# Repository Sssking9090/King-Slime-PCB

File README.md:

# King-Slime-PCB

 The project is a model of the King slime in Terraria. It also has the added function of vibrating and lighting up when the switch is clicked.
 
## Bill of meterials 
-  Resistors 6x
- 5mm LED 6x
 - mini motor disc
 - 6mm push button
 - CR2032 battery cell

Slack username: Sam

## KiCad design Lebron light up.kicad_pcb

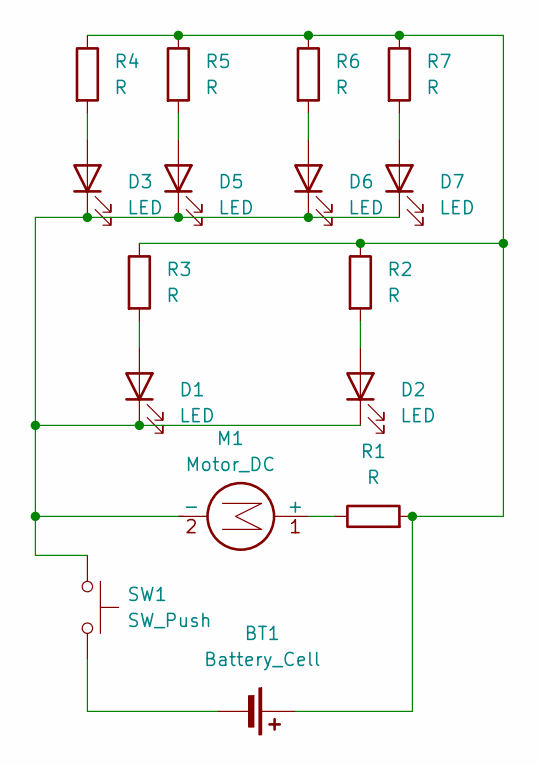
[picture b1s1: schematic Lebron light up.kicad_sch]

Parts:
BT1: Battery_Cell; BatteryHolder_Keystone_3034_1x20mm
D1, D2, D3, D5, D6, D7: LED; LED_D5.0mm
M1: Motor_DC; PinHeader_1x02_P2.54mm_Vertical
R1, R2, R3, R4, R5, R6, R7: R; R_Axial_DIN0207_L6.3mm_D2.5mm_P7.62mm_Horizontal
SW1: SW_Push; SW_PUSH_6mm

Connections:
unnamed: BT1.1 (+), R1.2, R2.1, R3.1, R4.1, R5.1, R6.1, R7.1
unnamed: BT1.2 (-), SW1.1
unnamed: D1.2 (A), R3.2
unnamed: D1.1 (K), D2.1 (K), D3.1 (K), D5.1 (K), D6.1 (K), D7.1 (K), M1.2 (-), SW1.2
unnamed: D2.2 (A), R2.2
unnamed: D3.2 (A), R4.2
unnamed: D5.2 (A), R5.2
unnamed: D6.2 (A), R6.2
unnamed: D7.2 (A), R7.2
unnamed: M1.1 (+), R1.1

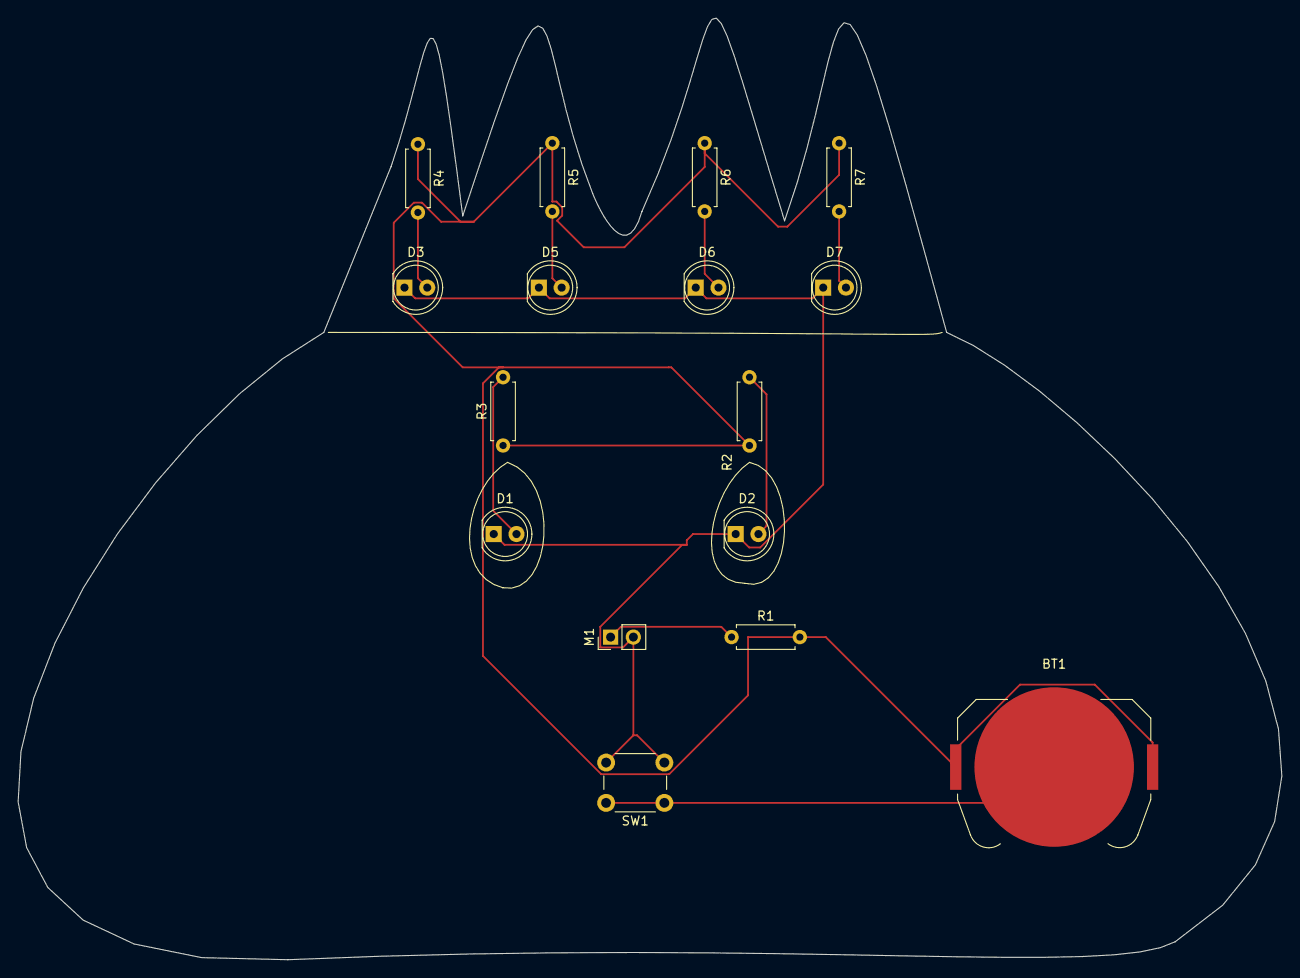
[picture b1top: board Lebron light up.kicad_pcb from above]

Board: 2 copper layers, 141.0 x 105.1 mm, 16 parts (0 on the bottom side), 10 nets.

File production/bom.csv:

Designator,Footprint,Quantity,Value,LCSC Part #
BT1,BatteryHolder_Keystone_3034_1x20mm,1,Battery_Cell,
"D1, D2, D3, D5, D6, D7",LED_D5.0mm,6,LED,
M1,PinHeader_1x02_P2.54mm_Vertical,1,Motor_DC,
"R1, R2, R3, R4, R5, R6, R7",R_Axial_DIN0207_L6.3mm_D2.5mm_P7.62mm_Horizontal,7,R,
SW1,SW_PUSH_6mm,1,SW_Push,

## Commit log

2025-05-05 King-Slime-PCB
2025-05-06 Recreated the Desgin to make it smaller and add a image.
2025-05-06 Fixed the crown by removing the pointy edges
